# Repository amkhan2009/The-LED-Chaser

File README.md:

This is the LED Chaser from the Statis Starter Guide. I have made it my own by giving it a custom body and text.

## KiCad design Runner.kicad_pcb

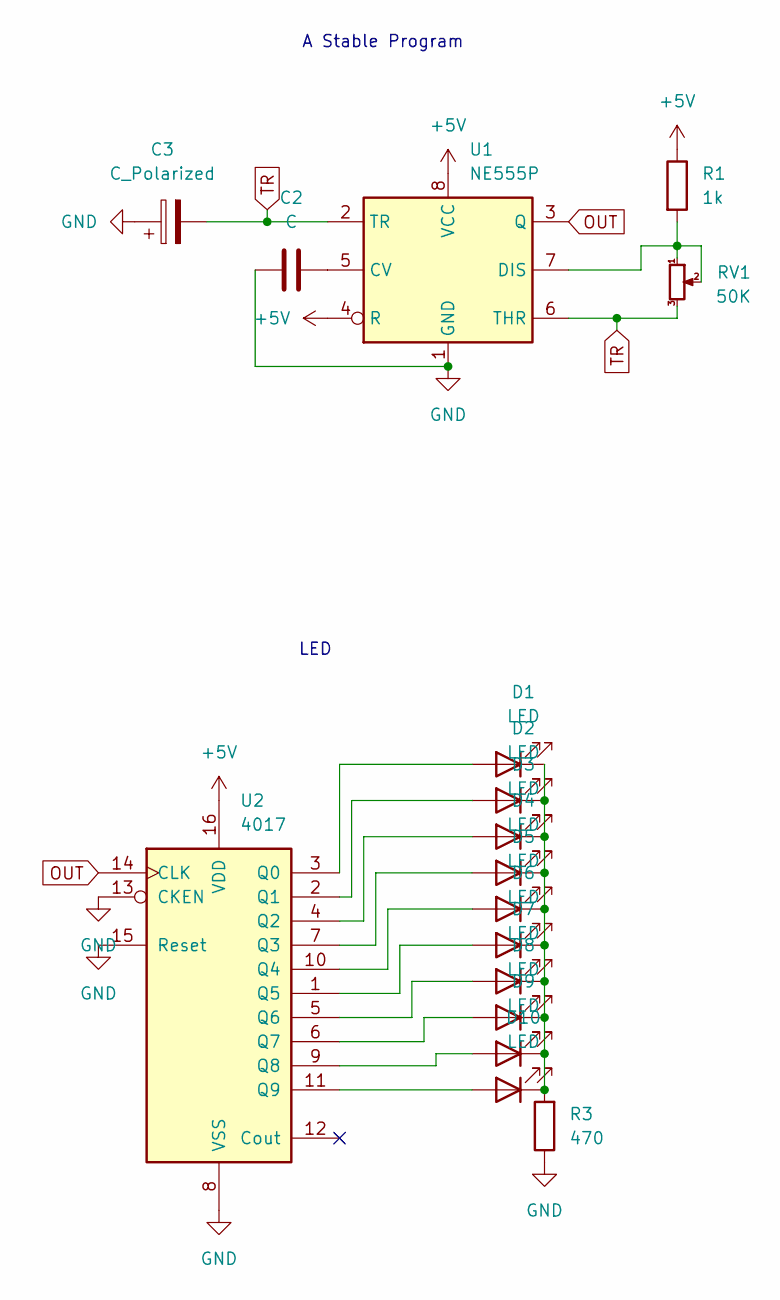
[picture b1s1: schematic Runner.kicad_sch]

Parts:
C2: C; CP_Radial_D5.0mm_P2.00mm
C3: C_Polarized; C_Disc_D7.5mm_W2.5mm_P5.00mm
D1, D2, D3, D4, D5, D6, D7, D8, D9, D10: LED; LED_D3.0mm
R1: 1k; R_Axial_DIN0207_L6.3mm_D2.5mm_P7.62mm_Horizontal
R3: 470; R_Axial_DIN0207_L6.3mm_D2.5mm_P7.62mm_Horizontal
RV1: 50K; Potentiometer_Vishay_T93YA_Vertical
U1: NE555P; DIP-8_W7.62mm
U2: 4017; N16

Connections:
+5V: R1.1, U1.4 (R), U1.8 (VCC), U2.16 (VDD)
GND: C2.1, C3.1, R3.1, U1.1 (GND), U2.8 (VSS), U2.13 (CKEN), U2.15 (Reset)
unnamed: D1.2 (A), U2.3 (Q0)
unnamed: D1.1 (K), D2.1 (K), D3.1 (K), D4.1 (K), D5.1 (K), D6.1 (K), D7.1 (K), D8.1 (K), D9.1 (K), D10.1 (K), R3.2
unnamed: D2.2 (A), U2.2 (Q1)
unnamed: D3.2 (A), U2.4 (Q2)
unnamed: D4.2 (A), U2.7 (Q3)
unnamed: D5.2 (A), U2.10 (Q4)
unnamed: D6.2 (A), U2.1 (Q5)
unnamed: D7.2 (A), U2.5 (Q6)
unnamed: D8.2 (A), U2.6 (Q7)
unnamed: D9.2 (A), U2.9 (Q8)
unnamed: D10.2 (A), U2.11 (Q9)
unnamed: C2.2, U1.5 (CV)
unnamed: R1.2, RV1.1, RV1.2, U1.7 (DIS)
OUT: U1.3 (Q), U2.14 (CLK)
TR: C3.2, RV1.3, U1.2 (TR), U1.6 (THR)

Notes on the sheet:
A Stable Program
LED

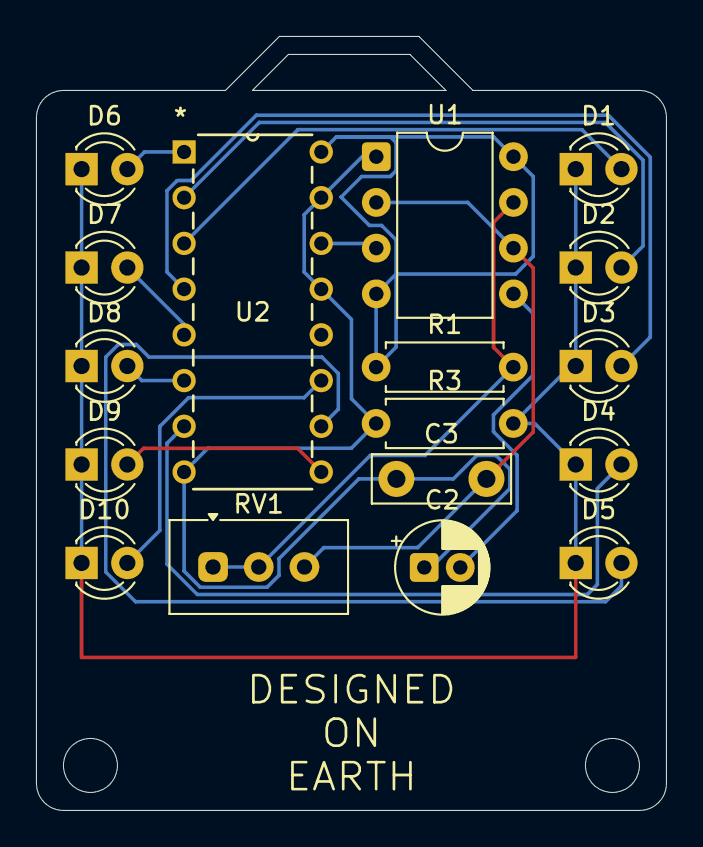
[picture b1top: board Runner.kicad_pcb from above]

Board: 2 copper layers, 35.0 x 43.0 mm, 17 parts (0 on the bottom side), 17 nets.

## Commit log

2026-04-05 Create Project
